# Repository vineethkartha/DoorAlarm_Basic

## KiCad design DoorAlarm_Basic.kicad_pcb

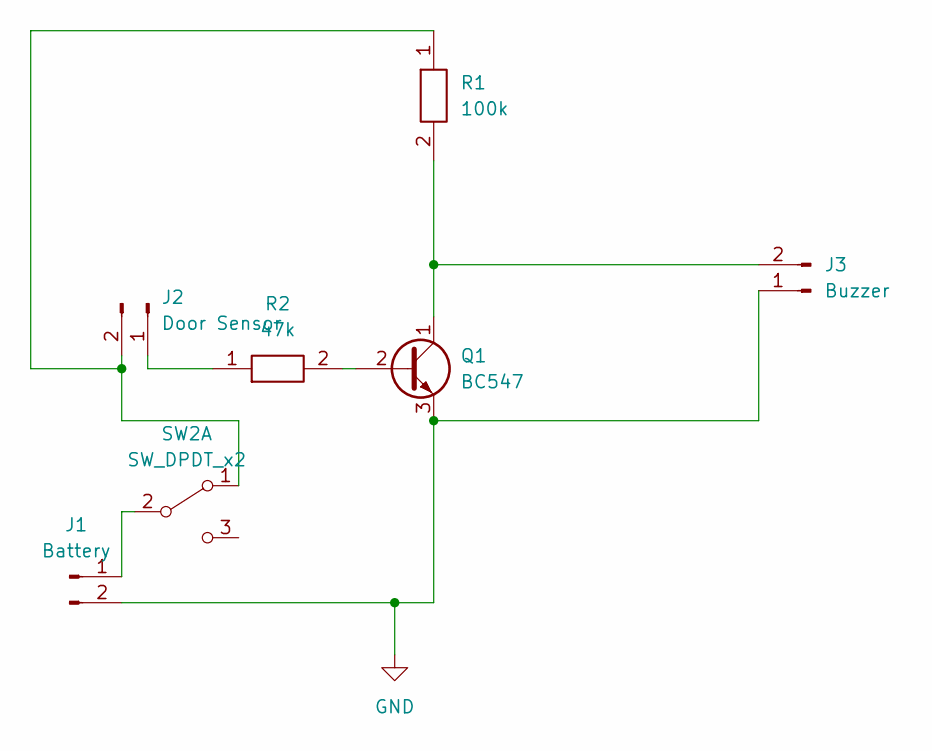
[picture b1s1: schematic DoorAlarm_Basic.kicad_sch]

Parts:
J1: Battery; PinSocket_1x02_P2.54mm_Horizontal
J2: Door Sensor; PinSocket_1x02_P2.54mm_Horizontal
J3: Buzzer; PinSocket_1x02_P2.54mm_Horizontal
Q1: BC547; TO-92_Inline
R1: 100k; R_Axial_DIN0204_L3.6mm_D1.6mm_P5.08mm_Horizontal
R2: 47k; R_Axial_DIN0204_L3.6mm_D1.6mm_P5.08mm_Horizontal
SW2: SW_DPDT_x2; SW_CuK_JS202011CQN_DPDT_Straight

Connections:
GND: J1.2, J3.1, Q1.3 (E)
unnamed: J1.1, SW2.2 (B)
unnamed: J2.1, R2.1
unnamed: J2.2, R1.1, SW2.1 (A)
unnamed: J3.2, Q1.1 (C), R1.2
unnamed: Q1.2 (B), R2.2

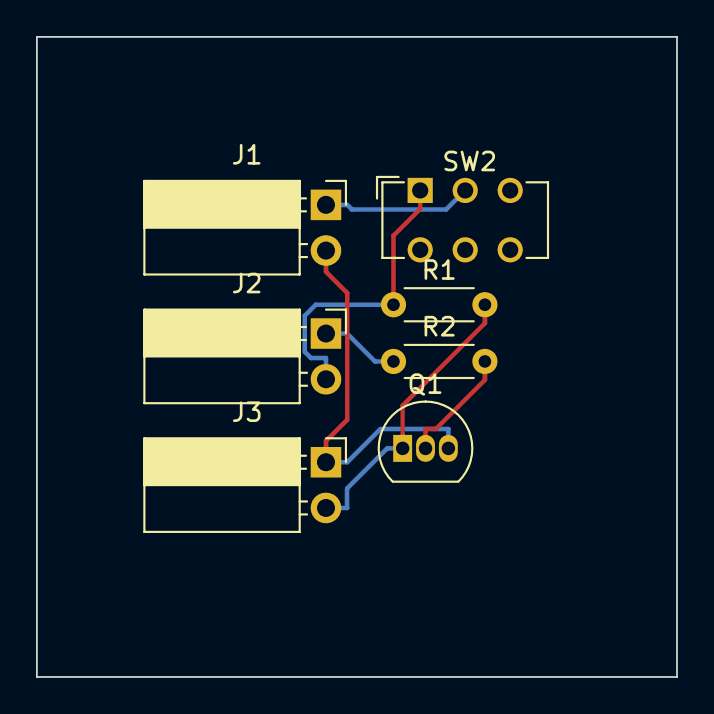
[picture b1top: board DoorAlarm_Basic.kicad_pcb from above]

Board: 2 copper layers, 35.6 x 35.6 mm, 7 parts (0 on the bottom side), 6 nets.

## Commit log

2023-12-17 Initial Submit for the door alarm circuit
